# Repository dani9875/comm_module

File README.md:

# Jules Audio codec hat

## Cloning the Repository

To get started, clone the repository and initialize submodules:

```sh
git clone --recurse-submodules <repository-url>
cd <repository-name>
```

If the submodules are not initialized, run:
```sh
git submodule update --init --recursive
```

## Adding the Component Library to KiCad

### Symbol Library

1. Open KiCad and navigate to **Preferences > Manage Symbol Libraries**.
2. Under the **Global Libraries** tab, click **Add existing library**.
3. Locate and select the symbol library file:
   ```
   root/kicad_components/pepy_sym_lib.kicad_sym
   ```
4. Click **OK** to confirm.

### Footprint Library

1. Open KiCad and navigate to **Preferences > Manage Footprint Libraries**.
2. Under the **Global Libraries** tab, click **Add existing library**.
3. Locate and select the footprint library folder:
   ```
   root/kicad_components/pepy_sim_lib.pretty
   ```
4. Click **OK** to confirm.

Your component library is now added to KiCad and ready for use.

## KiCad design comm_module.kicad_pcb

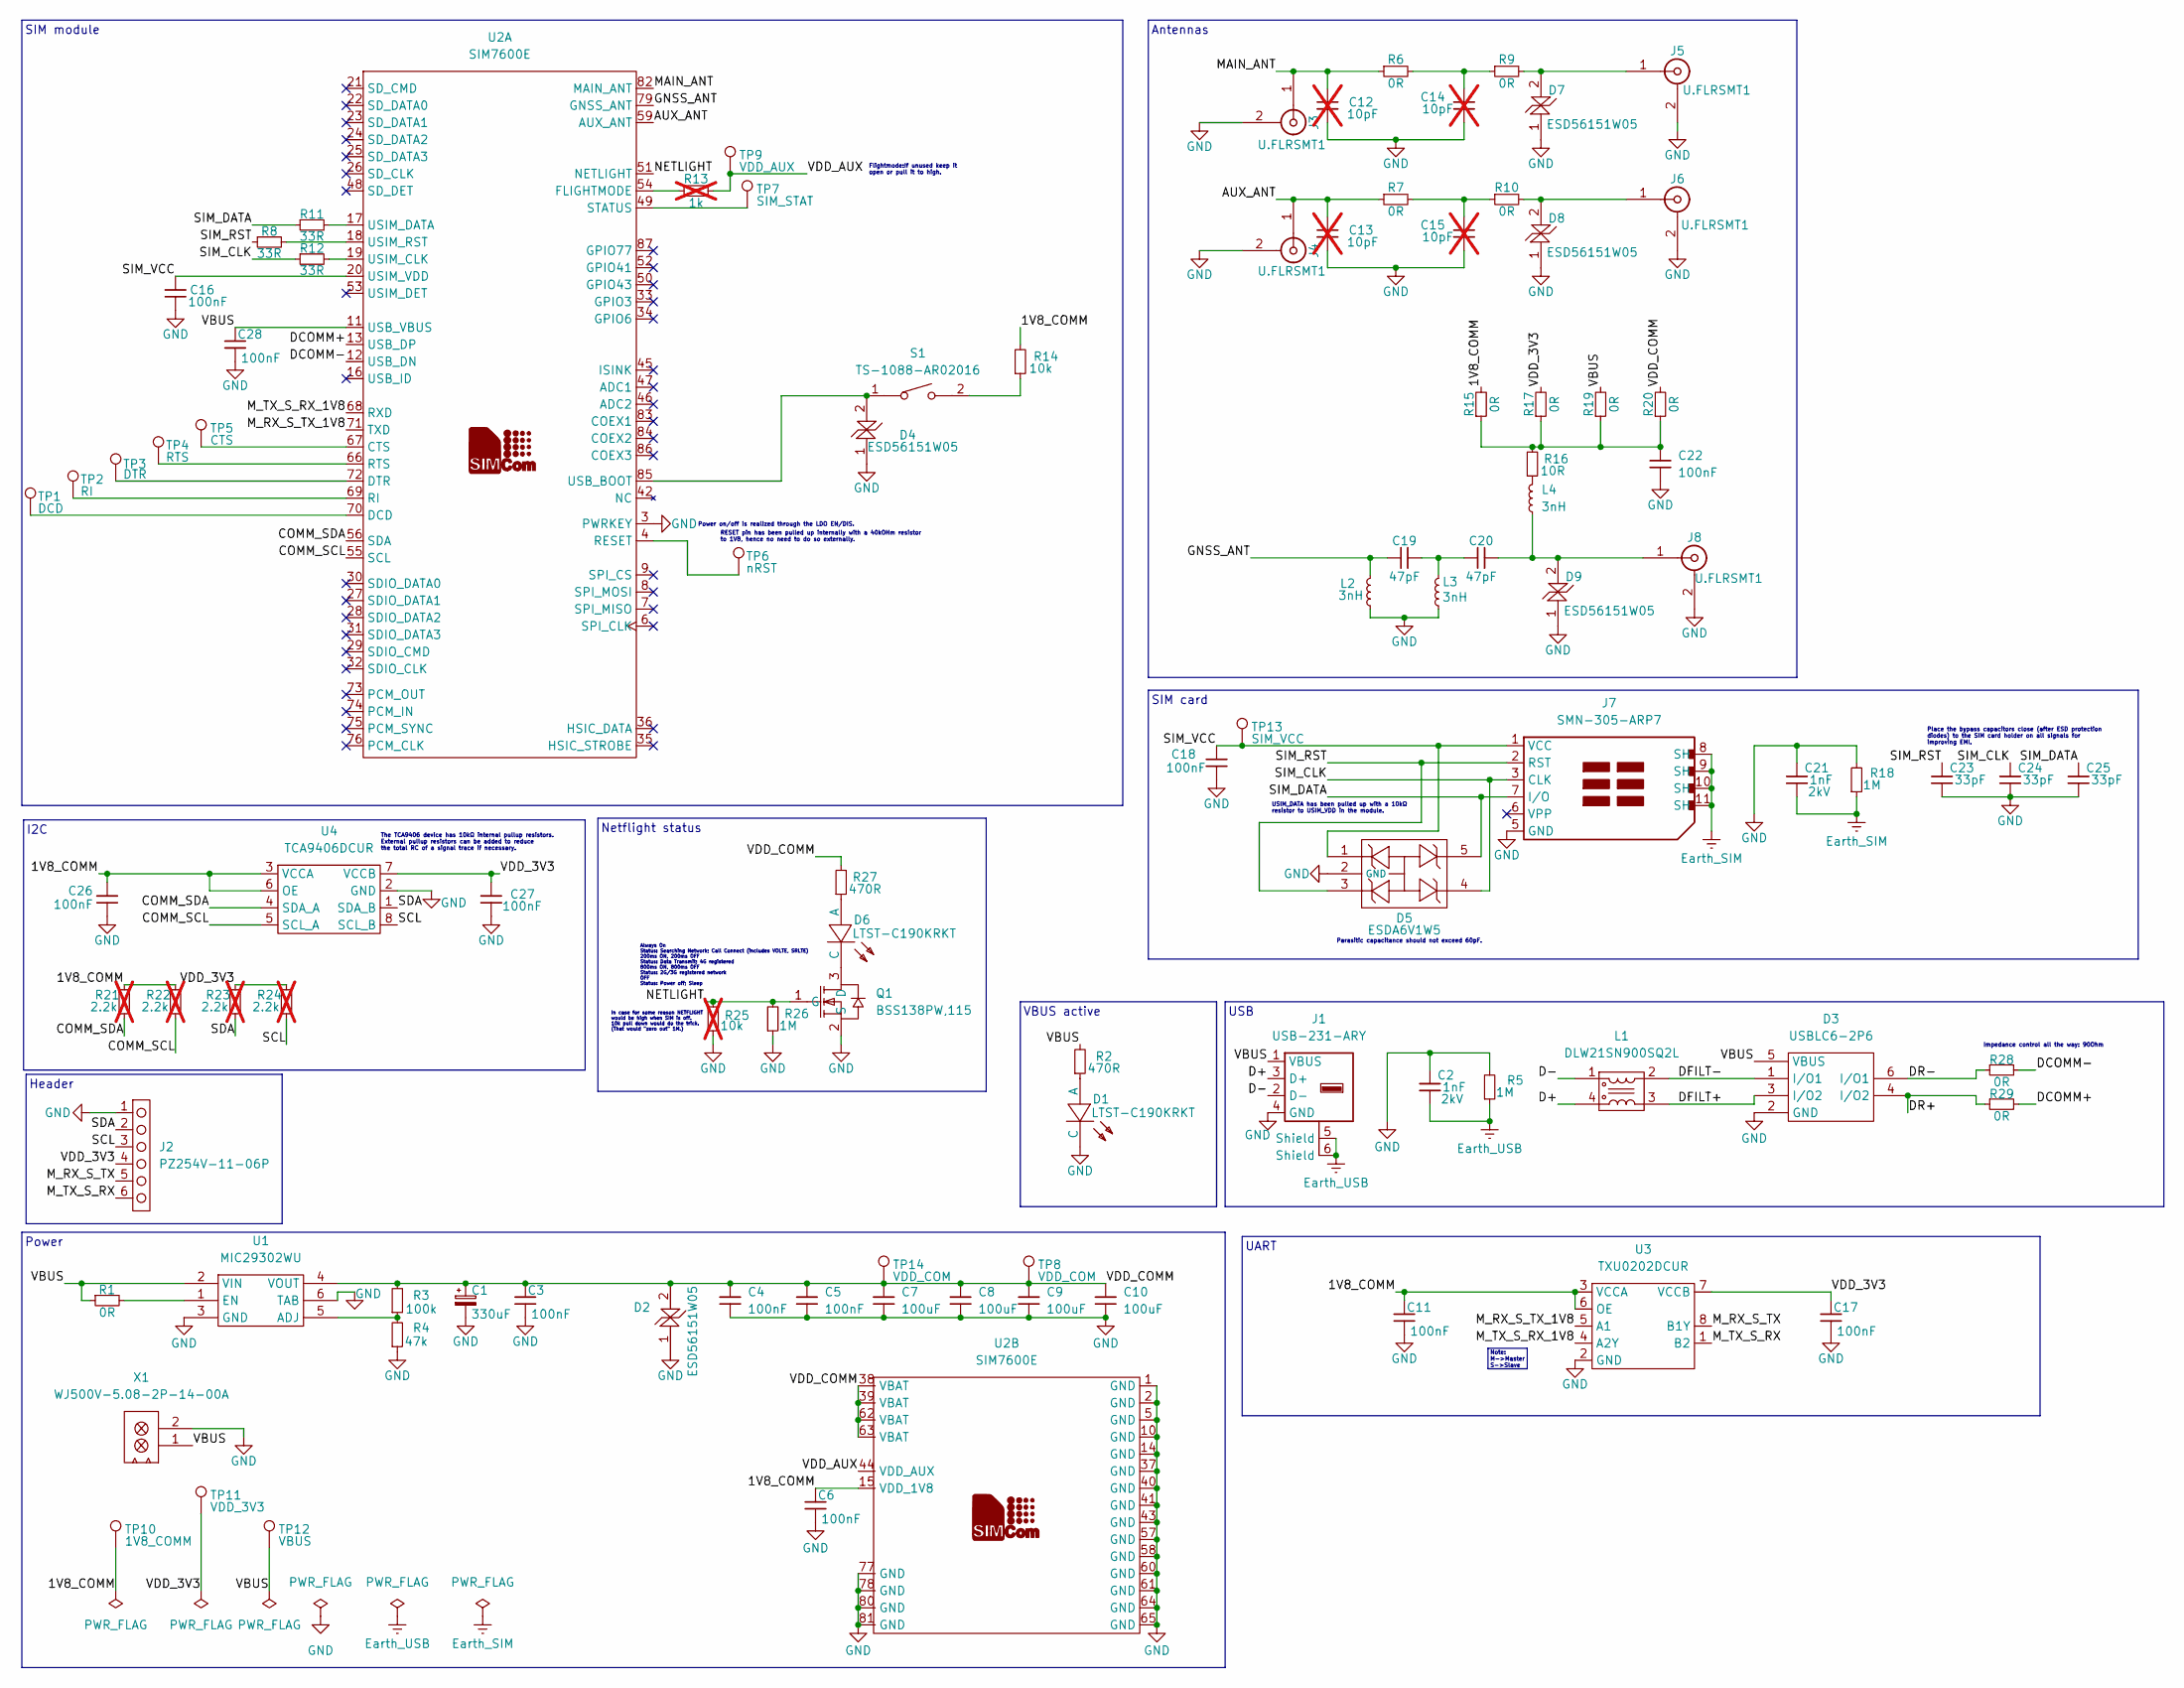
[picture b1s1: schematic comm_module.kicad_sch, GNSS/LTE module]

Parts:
C1: RVT1A331M0607; [CAP_SMD_AL_ELECTROLYTIC]ROQANG RVT1A331M0607; Voltage rating 10V; Tolerance 20%; LCSC Part C7419412
C2, C21: CC1206KKX7RDBB102; [CAP_SMD_1206_3216Metric]; Tolerance ±10%; Voltage rating 2kV; LCSC Part C23631
C3, C4, C5, C6, C11, C16, C17, C18, C26, C27, C28: CC0201KRX5R6BB104; [CAP_SMD_0201_0603Metric]; Tolerance ±10%; Voltage rating 10V; LCSC Part C190183
C7, C8, C9, C10: CL31A107MQHNNNE; [CAP_SMD_1206_3216Metric]; Tolerance ±20%; Voltage rating 6.3V; LCSC Part C15008
C12, C13, C14, C15: GRM0335C1H100JA01D; [CAP_SMD_0201_0603Metric]; Tolerance ±5%; Voltage rating 50V; LCSC Part C76921; not fitted
C19, C20: GRM0335C1H470JA01D; [CAP_SMD_0201_0603Metric]; Tolerance ±5%; Voltage rating 50V; LCSC Part C85908
C22: CC0402KRX7R7BB104; [CAP_SMD_0402_1005Metric]; Tolerance ±10%; Voltage rating 16V; LCSC Part C60474
C23, C24, C25: GRM0335C1H330JA01D; [CAP_SMD_0201_0603Metric]; Tolerance ±5%; Voltage rating 50V; LCSC Part C76925
D1, D6: LTST-C190KRKT; [LED]Lite-On LTST-C190KRKT; LCSC Part C94869
D2, D4, D7, D8, D9: ESD56151W05; [ESD_PROT]WILLSEMI ESD56151W05-2TR; LCSC Part C915918
D3: USBLC6-2P6; [ESD_PROT]STMicroelectronics USBLC6-2P6; LCSC Part C15999
D5: ESDA6V1W5; [ESD_PROT]TECH PUBLIC ESDA6V1W5; LCSC Part C3040609
J1: USB-231-ARY; [USB_A_4P_RA_FEMALE]XUNPU USB-231-ARY; LCSC Part C720525
J2: PZ254V-11-06P; [6P_HEADER_STR]XFCN PZ254V-11-06P; LCSC Part C492405
J3, J4, J5, J6, J8: U.FLRSMT1; [SMD_COAXIAL_CONNECTOR]HRS(Hirose) U.FL-R-SMT-1(80); LCSC Part C88374
J7: SMN-305-ARP7; [U_SIM]XUNPU SMN-305-ARP7; LCSC Part C720512
L1: DLW21SN900SQ2L; [COMMON_MODE_FILTER]Murata Electronics DLW21SN900SQ2L; LCSC Part C97856
L2, L3, L4: LQG15HS3N0S02D; [IND_SMD_0402_1005Metric]; LCSC Part C19898
Q1: BSS138PW,115; [NMOS]Nexperia BSS138PW,115; LCSC Part C193366
R1, R6, R7, R9, R10, R28, R29: 0402WGF0000TCE; [RES_SMD_0402_1005Metric]; Tolerance 1%; LCSC Part C17168
R2, R27: RC0201FR-07470RL; [RES_SMD_0201_0603Metric]; Tolerance 1%; LCSC Part C295802
R3: RC0402FR-07100KL; [RES_SMD_0402_1005Metric]; Tolerance 1%; LCSC Part C60491
R4: 0402WGF4702TCE; [RES_SMD_0402_1005Metric]; Tolerance 1%; LCSC Part C25792
R5, R18: 0805W8F1004T5E; [RES_SMD_0805_2012Metric]; Tolerance 1%; LCSC Part C17514
R8, R11, R12: RC0201FR-0733RL; [RES_SMD_0201_0603Metric]; Tolerance 1%; LCSC Part C295794
R13: RC0402FR-071KL; [RES_SMD_0402_1005Metric]; Tolerance 1%; LCSC Part C106235; not fitted
R14: 0201WMF1002TEE; [RES_SMD_0201_0603Metric]; Tolerance 1%; LCSC Part C473048
R15, R17, R19, R20: 0805W8F0000T5E; [RES_SMD_0805_2012Metric]; Tolerance 1%; LCSC Part C17477
R16: RC0603FR-0710RL; [RES_SMD_0603_1608Metric]; Tolerance 1%; LCSC Part C109318
R21, R22, R23, R24: 0402WGF2201TCE; [RES_SMD_0402_1005Metric]; Tolerance 1%; LCSC Part C25879; not fitted
R25: 0201WMF1002TEE; [RES_SMD_0201_0603Metric]; Tolerance 1%; LCSC Part C473048; not fitted
R26: RC0201FR-071ML; [RES_SMD_0201_0603Metric]; Tolerance 1%; LCSC Part C295786
S1: TS-1088-AR02016; [TACTILE_SWITCH]XUNPU TS-1088-AR02016; LCSC Part C720477
TP1: DCD; [TEST_POINT]TestPoint_Pad_D1.0mm
TP2: RI; [TEST_POINT]TestPoint_Pad_D1.0mm
TP3: DTR; [TEST_POINT]TestPoint_Pad_D1.0mm
TP4: RTS; [TEST_POINT]TestPoint_Pad_D1.0mm
TP5: CTS; [TEST_POINT]TestPoint_Pad_D1.0mm
TP6: nRST; [TEST_POINT]TestPoint_Pad_D1.0mm
TP7: SIM_STAT; [TEST_POINT]TestPoint_Pad_D1.0mm
TP8, TP14: VDD_COM; [TEST_POINT]TestPoint_Pad_D1.0mm
TP9: VDD_AUX; [TEST_POINT]TestPoint_Pad_D1.0mm
TP10: 1V8_COMM; [TEST_POINT]TestPoint_Pad_D1.0mm
TP11: VDD_3V3; [TEST_POINT]TestPoint_Pad_D1.0mm
TP12: VBUS; [TEST_POINT]TestPoint_Pad_D1.0mm
TP13: SIM_VCC; [TEST_POINT]TestPoint_Pad_D1.0mm
U1: MIC29302WU; [LDO]MICROCHIP MIC29302WU-TR; LCSC Part C11149
U2: SIM7600E; [GSM_3G_LTE]SIMCom Wireless Solutions SIM7600E; LCSC Part C2995536
U3: TXU0202DCUR; [LEVEL_SHIFTER]TI TXU0202DCUR; LCSC Part C5186957
U4: TCA9406DCUR; [LEVEL_SHIFTER]TI TCA9406DCUR; LCSC Part C840107
X1: WJ500V-5.08-2P-14-00A; [1x2_SCREW_TERMINAL_BLOCK]Ningbo Kangnex Elec WJ500V-5.08-2P; LCSC Part C8465

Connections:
/1V8_COMM: C6.2, C11.2, C26.1, R14.2, R15.2, R21.2, R22.2, TP10.1, U2.15 (VDD_1V8), U3.3 (VCCA), U3.6 (OE), U4.3 (VCCA), U4.6 (OE)
/AUX_ANT: C13.2, J4.1, R7.1, U2.59 (AUX_ANT)
/COMM_SCL: R22.1, U2.55 (SCL), U4.5 (SCL_A)
/COMM_SDA: R21.1, U2.56 (SDA), U4.4 (SDA_A)
/D+: J1.3 (D+), L1.4
/D-: J1.2 (D-), L1.1
/DCOMM+: R29.2, U2.13 (USB_DP)
/DCOMM-: R28.2, U2.12 (USB_DN)
/DFILT+: D3.3 (I/O2), L1.3
/DFILT-: D3.1 (I/O1), L1.2
/DR+: D3.4 (I/O2), R29.1
/DR-: D3.6 (I/O1), R28.1
/GNSS_ANT: C19.1, L2.2, U2.79 (GNSS_ANT)
/MAIN_ANT: C12.2, J3.1, R6.1, U2.82 (MAIN_ANT)
/M_RX_S_TX: J2.5, U3.8 (B1Y)
/M_RX_S_TX_1V8: U2.71 (TXD), U3.5 (A1)
/M_TX_S_RX: J2.6, U3.1 (B2)
/M_TX_S_RX_1V8: U2.68 (RXD), U3.4 (A2Y)
/NETLIGHT: Q1.1 (G), R25.2, R26.2, U2.51 (NETLIGHT)
/SCL: J2.3, R24.1, U4.8 (SCL_B)
/SDA: J2.2, R23.1, U4.1 (SDA_B)
/SIM_CLK: C24.2, D5.4, J7.3 (CLK), R12.1
/SIM_DATA: C25.2, D5.5, J7.7 (I/O), R11.1
/SIM_RST: C23.2, D5.3, J7.2 (RST), R8.1
/SIM_VCC: C16.2, C18.2, D5.1, J7.1 (VCC), TP13.1, U2.20 (USIM_VDD)
/VBUS: C28.2, D3.5 (VBUS), J1.1 (VBUS), R1.1, R2.2, R19.2, TP12.1, U1.2 (VIN), U2.11 (USB_VBUS), X1.1
/VDD_3V3: C17.2, C27.1, J2.4, R17.2, R23.2, R24.2, TP11.1, U3.7 (VCCB), U4.7 (VCCB)
/VDD_AUX: R13.2, TP9.1, U2.44 (VDD_AUX)
/VDD_COMM: C1.1, C3.2, C4.2, C5.2, C7.2, C8.2, C9.2, C10.2, D2.2 (A), R3.2, R20.2, R27.2, TP8.1, TP14.1, U1.4 (VOUT), U2.38 (VBAT), U2.39 (VBAT), U2.62 (VBAT), U2.63 (VBAT)
Earth_SIM: C21.1, J7.8 (SH), J7.9 (SH), J7.10 (SH), J7.11 (SH), R18.1
Earth_USB: C2.1, J1.5 (Shield), J1.6 (Shield), R5.1
GND: C1.2, C2.2, C3.1, C4.1, C5.1, C6.1, C7.1, C8.1, C9.1, C10.1, C11.1, C12.1, C13.1, C14.1, C15.1, C16.1, C17.1, C18.1, C21.2, C22.1, C23.1, C24.1, C25.1, C26.2, C27.2, C28.1, D1.2 (C), D2.1 (C), D3.2 (GND), D4.1 (C), D5.2 (GND), D7.1 (C), D8.1 (C), D9.1 (C), J1.4 (GND), J2.1, J3.2, J4.2, J5.2, J6.2, J7.5 (GND), J8.2, L2.1, L3.1, Q1.2 (S), R4.1, R5.2, R18.2, R25.1, R26.1, U1.3 (GND), U1.6 (TAB), U2.1 (GND), U2.2 (GND), U2.3 (PWRKEY), U2.5 (GND), U2.10 (GND), U2.14 (GND), U2.37 (GND), U2.40 (GND), U2.41 (GND), U2.43 (GND), U2.57 (GND), U2.58 (GND), U2.60 (GND), U2.61 (GND), U2.64 (GND), U2.65 (GND), U2.77 (GND), U2.78 (GND), U2.80 (GND), U2.81 (GND), U3.2 (GND), U4.2 (GND), X1.2
unnamed: C14.2, R6.2, R9.1
unnamed: C15.2, R7.2, R10.1
unnamed: C19.2, C20.1, L3.2
unnamed: C22.2, R15.1, R16.2, R17.1, R19.1, R20.1
unnamed: D1.1 (A), R2.1
unnamed: D4.2 (A), S1.1, U2.85 (USB_BOOT)
unnamed: D6.1 (A), R27.1
unnamed: D6.2 (C), Q1.3 (D)
unnamed: D7.2 (A), J5.1, R9.2
unnamed: D8.2 (A), J6.1, R10.2
unnamed: C20.2, D9.2 (A), J8.1, L4.1
unnamed: L4.2, R16.1
unnamed: R14.1, S1.2
unnamed: R3.1, R4.2, U1.5 (ADJ)
unnamed: R1.2, U1.1 (EN)
unnamed: TP5.1, U2.67 (CTS)
unnamed: TP1.1, U2.70 (DCD)
unnamed: TP3.1, U2.72 (DTR)
unnamed: R13.1, U2.54 (FLIGHTMODE)
unnamed: TP6.1, U2.4 (RESET)
unnamed: TP2.1, U2.69 (RI)
unnamed: TP4.1, U2.66 (RTS)
unnamed: TP7.1, U2.49 (STATUS)
unnamed: R12.2, U2.19 (USIM_CLK)
unnamed: R11.2, U2.17 (USIM_DATA)
unnamed: R8.2, U2.18 (USIM_RST)

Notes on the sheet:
USB
SIM card
Note: M->Master S->Slave
VBUS active
Header
Always On Status: Searching Network; Call Connect (includes VOLTE, SRLTE) 200ms ON, 200ms OFF Status: Data Transmit; 4G registered 800ms ON, 800ms OFF Status: 2G/3G registered network OFF Status: Power off; Sleep
The TCA9406 device has 10kΩ internal pullup resistors. External pullup resistors can be added to reduce the total RC of a signal trace if necessary.
Parasitic capacitance should not exceed 60pF.
Place the bypass capacitors close (after ESD protection diodes) to the SIM card holder on all signals for improving EMI.
Impedance control all the way: 90Ohm
UART
Power on/off is realized through the LDO EN/DIS.
Antennas
Netflight status
Power
USIM_DATA has been pulled up with a 10kΩ resistor to USIM_VDD in the module.
RESET pin has been pulled up internally with a 40kOHm resistor to 1V8, hence no need to do so externally.
I2C
Flightmode:If unused keep it open or pull it to high.
SIM module
In case for some reason NETFLIGHT would be high when SIM is off. 10k pull down would do the trick. (That would "zero out" 1M.)

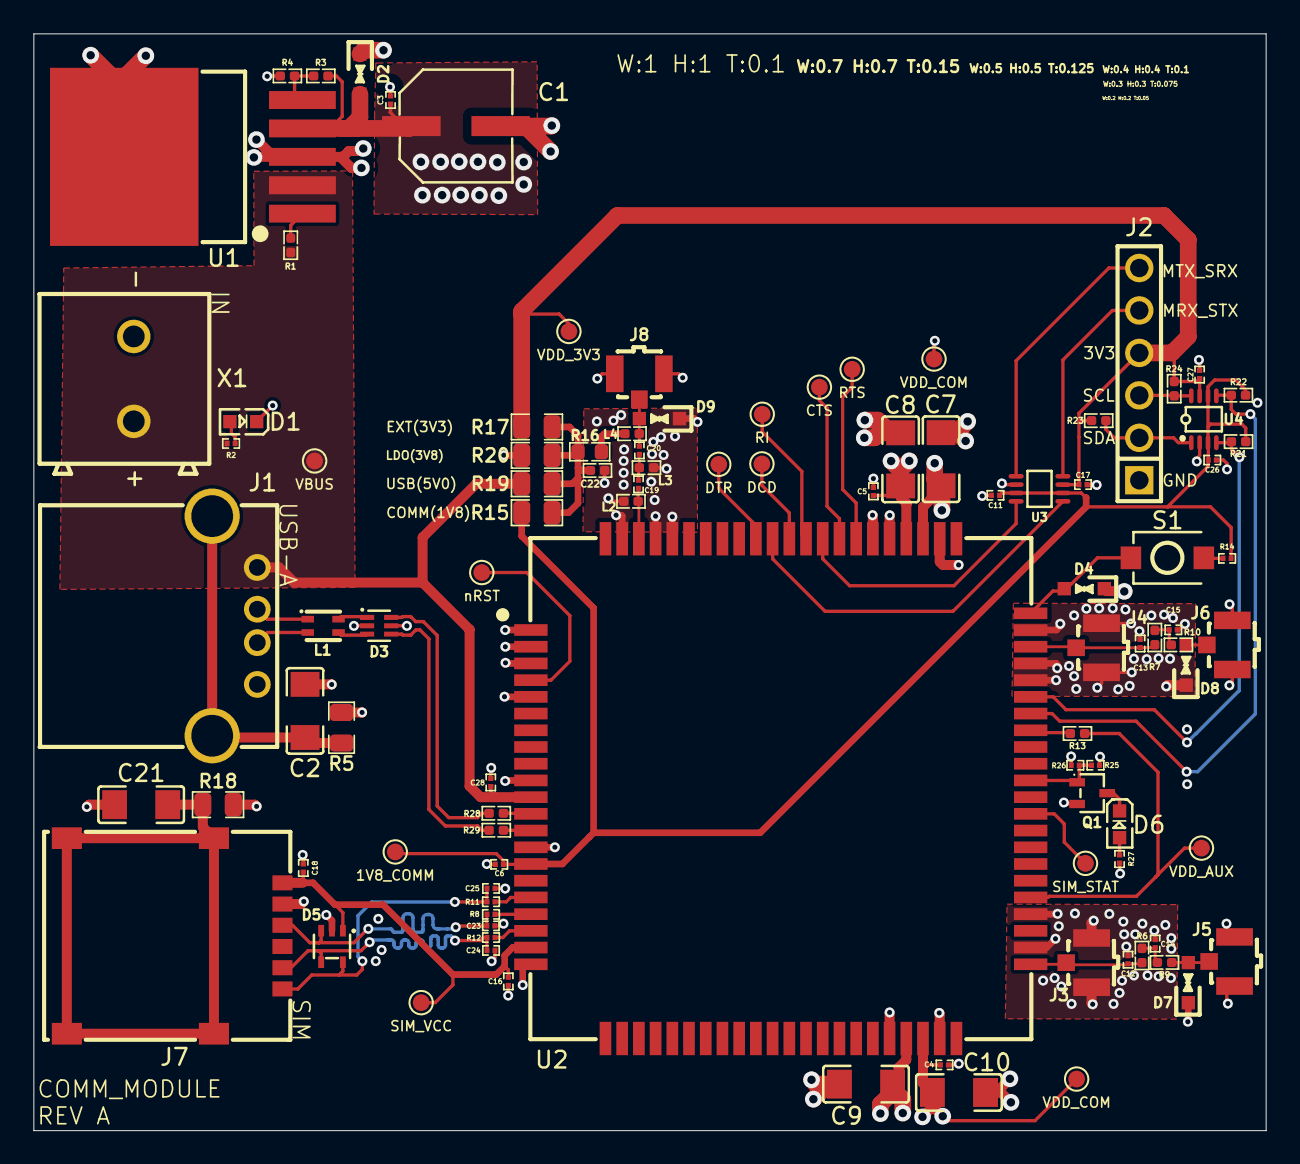
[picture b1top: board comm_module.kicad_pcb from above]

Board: 4 copper layers, 73.7 x 65.6 mm, 99 parts (0 on the bottom side), 58 nets.

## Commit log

2025-08-21 First no error draft
2025-08-21 Comp lib updated
2025-08-21 Reannotation
2025-08-22 Antenna polygon fixes and refinements
2025-08-22 Rev A
